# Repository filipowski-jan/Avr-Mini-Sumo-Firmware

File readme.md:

# Avr Mini Sumo Firmware

Firmware for an AVR-based mini sumo robot built around an ATmega8 running at 16 MHz.

## Behavior

The control loop in `main.c` follows this strategy:

- If the line sensor detects arena edge, the robot briefly retreats.
- If the IR sensor detects an opponent, the robot drives forward at full speed.
- Otherwise, the robot performs a search turn pattern.

## Project files

- `main.c` – main robot behavior loop.
- `motors.c` / `motors.h` – motor control functions.
- `ir_sensor.c` / `ir_sensor.h` – opponent detection sensor handling.
- `line_sensor.c` / `line_sensor.h` – arena edge detection sensor handling.

## Build

Use AVR-GCC and AVR binutils.

On Linux/macOS:

```bash
./build.sh
```

This generates:

- `main.elf`
- `main.hex`

## Flashing

Flash `main.hex` with your preferred AVR programmer (for example, `avrdude`) using settings that match your hardware.

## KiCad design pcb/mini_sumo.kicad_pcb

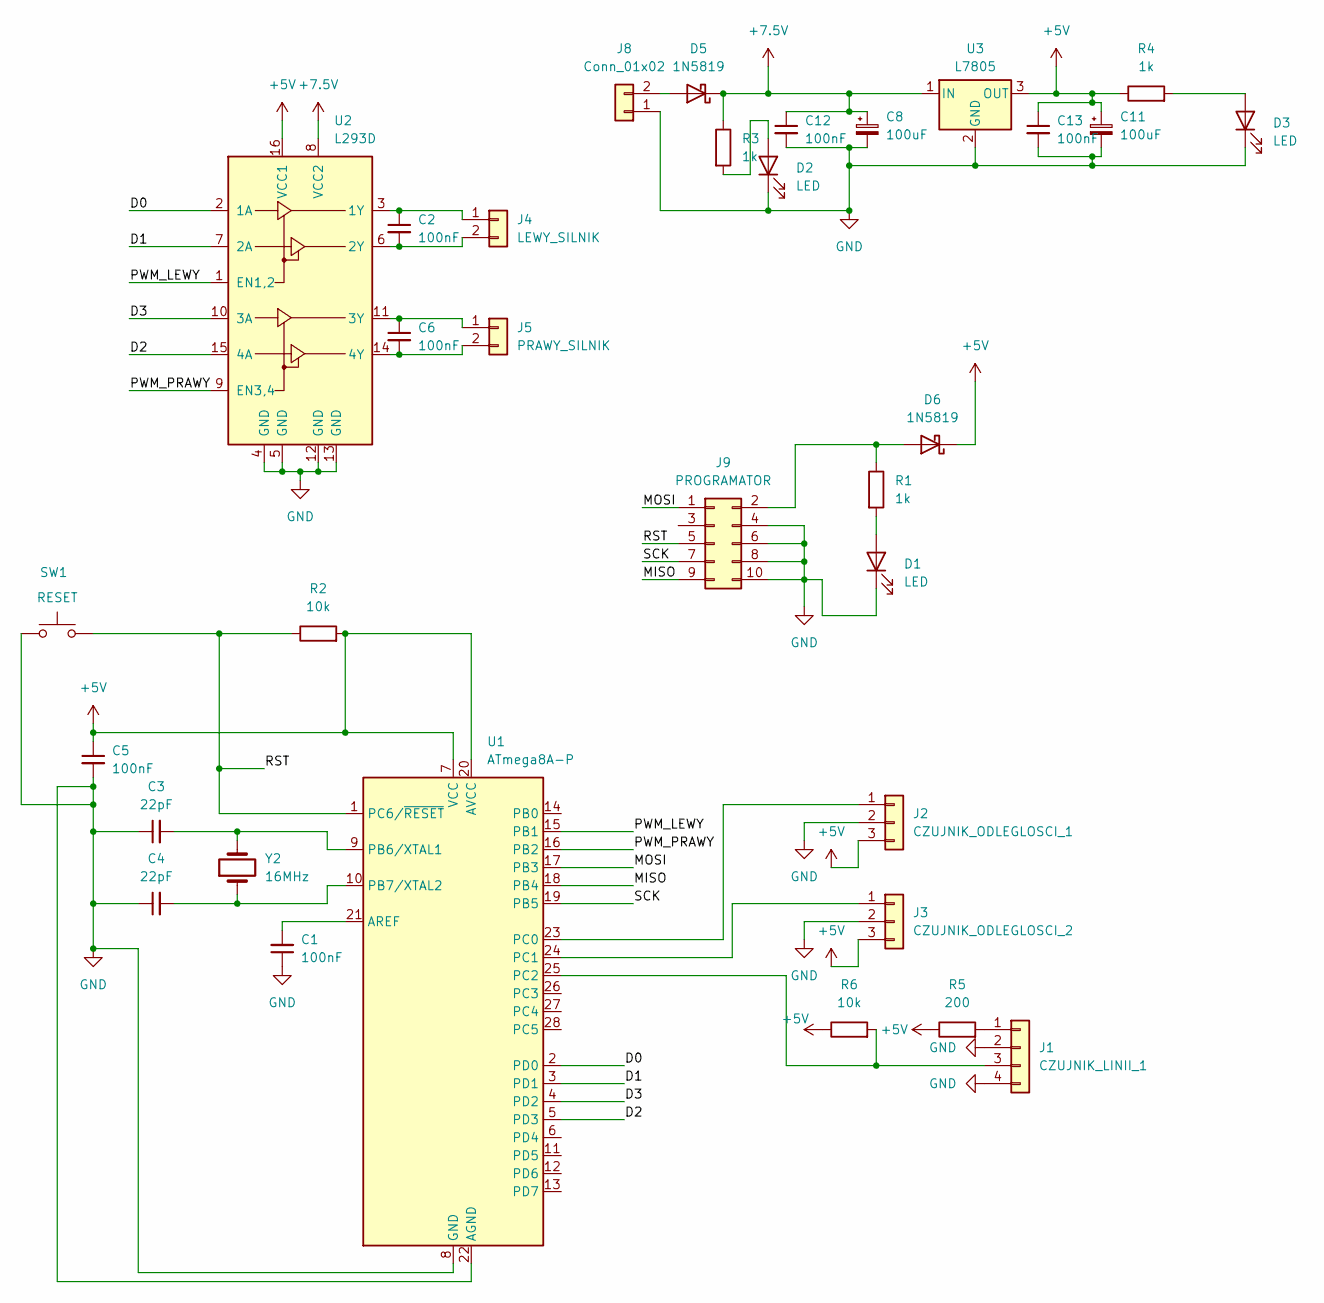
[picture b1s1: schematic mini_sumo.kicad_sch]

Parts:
C1, C2, C5, C6, C12, C13: 100nF; C_Disc_D5.0mm_W2.5mm_P5.00mm
C3, C4: 22pF; C_Disc_D5.0mm_W2.5mm_P5.00mm
C8, C11: 100uF; CP_Radial_D6.3mm_P2.50mm
D1, D2, D3: LED; LED_D3.0mm
D5, D6: 1N5819; D_DO-41_SOD81_P10.16mm_Horizontal
J1: CZUJNIK_LINII_1; PinHeader_1x04_P2.54mm_Vertical
J2: CZUJNIK_ODLEGLOSCI_1; PinHeader_1x03_P2.54mm_Vertical
J3: CZUJNIK_ODLEGLOSCI_2; PinHeader_1x03_P2.54mm_Vertical
J4: LEWY_SILNIK; TerminalBlock_Phoenix_MKDS-1,5-2-5.08_1x02_P5.08mm_Horizont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
J5: PRAWY_SILNIK; TerminalBlock_Phoenix_MKDS-1,5-2-5.08_1x02_P5.08mm_Horizont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
J8: Conn_01x02; TerminalBlock_Phoenix_MKDS-1,5-2-5.08_1x02_P5.08mm_Horizont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
J9: PROGRAMATOR; IDC-Header_2x05_P2.54mm_Vertical
R1, R3, R4: 1k; R_Axial_DIN0207_L6.3mm_D2.5mm_P10.16mm_Horizontal
R2, R6: 10k; R_Axial_DIN0207_L6.3mm_D2.5mm_P10.16mm_Horizontal
R5: 200; R_Axial_DIN0207_L6.3mm_D2.5mm_P10.16mm_Horizontal
SW1: RESET; SW_PUSH_6mm
U1: ATmega8A-P; DIP-28_W7.62mm
U2: L293D; DIP-16_W7.62mm
U3: L7805; TO-220-3_Vertical
Y2: 16MHz; Crystal_HC49-U_Vertical

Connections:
+5V: C5.1, C11.1, C13.1, D6.1 (K), J2.3, J3.3, R2.2, R4.1, R5.1, R6.1, U1.7 (VCC), U1.20 (AVCC), U2.16 (VCC1), U3.3 (OUT)
+7.5V: C8.1, C12.1, D5.1 (K), R3.1, U2.8 (VCC2), U3.1 (IN)
/D0: U1.2 (PD0), U2.2 (1A)
/D1: U1.3 (PD1), U2.7 (2A)
/D2: U1.5 (PD3), U2.15 (4A)
/D3: U1.4 (PD2), U2.10 (3A)
/MISO: J9.9, U1.18 (PB4)
/MOSI: J9.1, U1.17 (PB3)
/PWM_LEWY: U1.15 (PB1), U2.1 (EN1,2)
/PWM_PRAWY: U1.16 (PB2), U2.9 (EN3,4)
/RST: J9.5, R2.1, SW1.2, U1.1 (PC6/~RESET)
/SCK: J9.7, U1.19 (PB5)
GND: C1.1, C3.1, C4.1, C5.2, C8.2, C11.2, C12.2, C13.2, D1.1 (K), D2.1 (K), D3.1 (K), J1.2, J1.4, J2.2, J3.2, J8.1, J9.4, J9.6, J9.8, J9.10, SW1.1, U1.8 (GND), U1.22 (AGND), U2.4 (GND), U2.5 (GND), U2.12 (GND), U2.13 (GND), U3.2 (GND)
unnamed: D1.2 (A), R1.2
unnamed: D2.2 (A), R3.2
unnamed: D3.2 (A), R4.2
unnamed: D5.2 (A), J8.2
unnamed: D6.2 (A), J9.2, R1.1
unnamed: J1.1, R5.2
unnamed: J1.3, R6.2, U1.25 (PC2)
unnamed: J2.1, U1.23 (PC0)
unnamed: J3.1, U1.24 (PC1)
unnamed: C2.1, J4.1, U2.3 (1Y)
unnamed: C2.2, J4.2, U2.6 (2Y)
unnamed: C6.1, J5.1, U2.11 (3Y)
unnamed: C6.2, J5.2, U2.14 (4Y)
unnamed: C1.2, U1.21 (AREF)
unnamed: C3.2, U1.9 (PB6/XTAL1), Y2.2
unnamed: C4.2, U1.10 (PB7/XTAL2), Y2.1

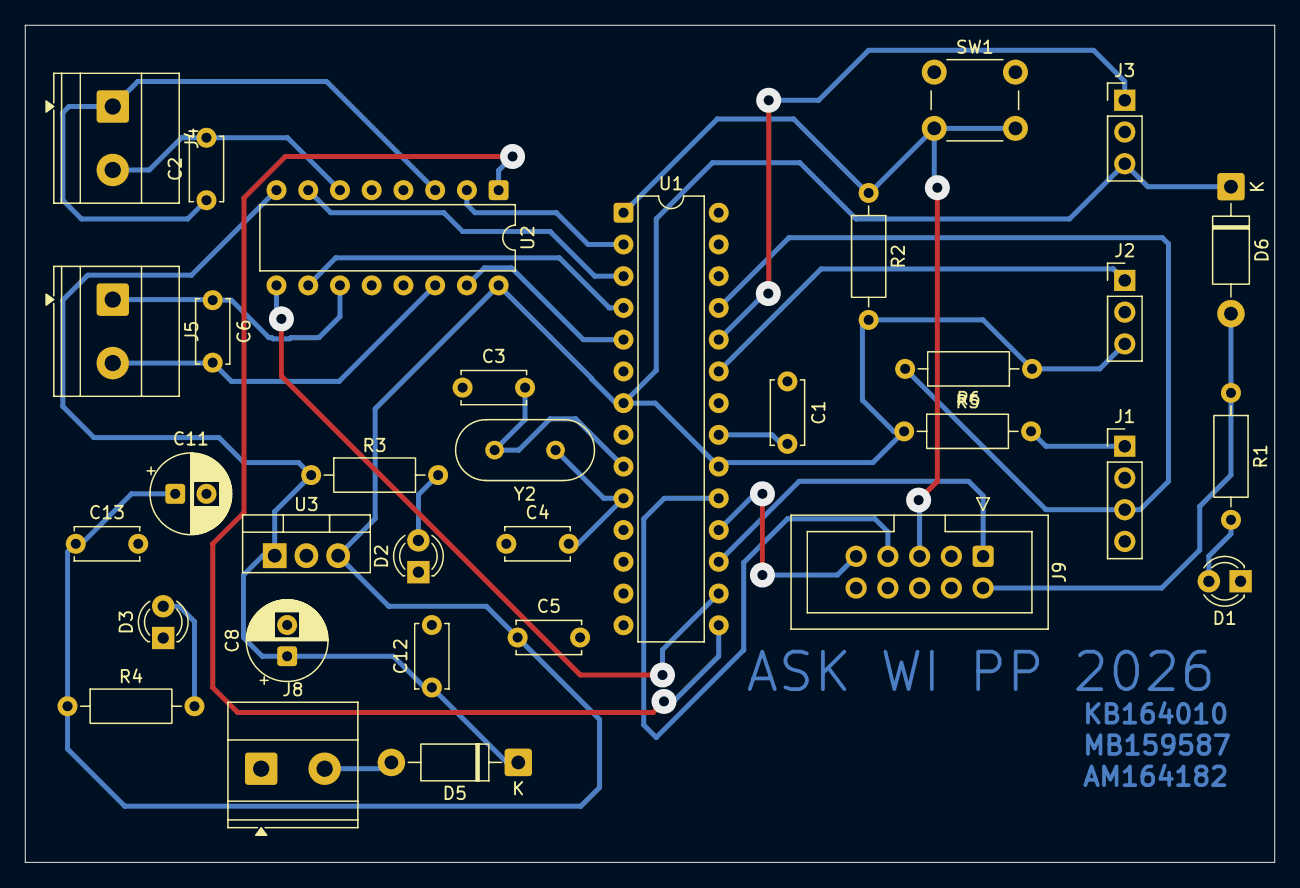
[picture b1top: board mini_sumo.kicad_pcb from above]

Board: 2 copper layers, 100.0 x 67.0 mm, 33 parts (0 on the bottom side), 29 nets.

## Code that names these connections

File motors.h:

#ifndef MOTORS_H
#define MOTORS_H

#include <avr/io.h>

// Motor direction pins
#define LEFT_IN1 PD0
#define LEFT_IN2 PD1
#define RIGHT_IN3 PD3
#define RIGHT_IN4 PD2
// Motor speed pins
#define LEFT_SPEED PB1
#define RIGHT_SPEED PB2

void motors_init(void);
void motor_left_forward(uint8_t speed);
void motor_right_forward(uint8_t speed);
void motor_left_backward(uint8_t speed);
void motor_right_backward(uint8_t speed);
void motors_stop(void);

#endif

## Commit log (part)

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2026-05-10 Initial commit, pcb desgin, build scripts, initial project structure
2026-05-10 Added motors logic, sensors logic and basic work algorithm
2026-05-11 Added searching
2026-05-13 Numbers Adjustments
